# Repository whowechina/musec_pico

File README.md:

# Musec Pico - MUSECA Style Mini Controller
[点这里可以切换到中文版](README_CN.md)

There're two versions. Musec Pico uses 52mm spinners and Musec Pico+ uses 74mm spinners. They have the same structure and function the same.

Features:
* It's small but closely replicates the feel of the arcade controller.
* Built-in "spacebar" pedal.
* External pedal support through the 3.5mm jack.
* Full HID light support.
* Command line for configurations.
* All source files open.

Thanks to many respectful guys/companies who made their tools or materials free or open source (KiCad, OnShape, InkScape, Raspberry things).

Special thanks to community projects and developers.
And also these projects:
* RP_Silicon_KiCad: https://github.com/HeadBoffin/RP_Silicon_KiCad
* Type-C: https://github.com/ai03-2725/Type-C.pretty

## My Other Projects
You can check out my other cool projects.

* Popn Pico: https://github.com/whowechina/popn_pico
* IIDX Pico: https://github.com/whowechina/iidx_pico
* IIDX Teeny: https://github.com/whowechina/iidx_teeny
* Chu Pico: https://github.com/whowechina/chu_pico
* Mai Pico: https://github.com/whowechina/mai_pico
* Diva Pico: https://github.com/whowechina/diva_pico
* AIC Pico: https://github.com/whowechina/aic_pico
* Groove Pico: https://github.com/whowechina/groove_pico
* Geki Pico: https://github.com/whowechina/geki_pico
* Musec Pico: https://github.com/whowechina/musec_pico
* Ju Pico: https://github.com/whowechina/ju_pico
* Bishi Pico: https://github.com/whowechina/bishi_pico
* Nos Pico: https://github.com/whowechina/nos_pico

## **Disclaimer** ##
I made this project in my personal time with no financial benefit or sponsorship. I will continue to improve the project. I have done my best to ensure that everything is accurate and functional, there's always a chance that mistakes may occur. I cannot be held responsible for any loss of your time or money that may result from using this open source project. Thank you for your understanding.

## About the License
It's CC-NC. So DIY for yourself and for your friend, don't make money from it. And plagiarism that doesn’t even dare to mention the original author is not acceptable. Plase note that pooling orders and group buying for raw materials is acceptable. Selling off any leftover components without profit is also acceptable.

If you're interested in buying from me or some kind of commercial use, please contact me (Discord, QQ group, Wechat group or leave your contact in issue section).

## My Discord Invitation
https://discord.gg/M8f2PPQFEA

## HOW TO BUILD
### PCB and Components
* Go JLCPCB and make order with the gerber zip files (latest `Production\PCB\musec_pico_xxx.zip` for Musec Pico or `Production\PCB\musec_plus_xxx.zip` for Musec Pico+, and `Procution\PCB\musec_pedal_xxx.zip` for both versions), regular FR-4 board, black or white color, **1.6mm** thickness.  
  
* 1x Rasberry Pico Pi Pico or pin-to-pin compatible clones (U1).  
  https://www.raspberrypi.com/products/raspberry-pi-pico
* 1x USB Type-C socket (918-418K2023S40001 or KH-TYPE-C-16P)
* 28x WS2812B-3528 RGB LEDs (all RGB LEDs).
* 6x TMAG5273, all device versions (such as A1, B2, etc.) works, SOT23-6 (U3 to U7).  
* 12x 0603 0.1uF (0.1~1uF all fine) capacitors (all Capacitors).
* 2x 0603 5.1kohm resistors (R1, R2) for the USB.
* 2x 0603 5.1kohm resistors (R3, R4, 1k-20kohm all work fine) for I2C pull-up.
* 2x PJ-313 through-hole 3.5mm audio jacks (J2, J3).  
* 12x JST-SH1.0 4-pin right angle SMD connectors (JA1 to JA5, JB1 to JB5, Pedal, J1 on pedal board).  
  https://www.amazon.com/Kidisoii-Connector-Mounting-Vertical-SH1-0-SMT-Ver/dp/B0CQ28CCQG?th=1
* 6x JST-SH1.0 dual-end 4-pin cables, 60mm length * 5, and 100mm length * 1.
   The connector footprint on PCB also supports hand soldering. So if you can't find the connectors or the cables, you can solder the wires directly to the PCB.  
   RC hobby sites often have SH1.0 4P silicone cables, but with only one end connector. You can solder the other end to the PCB. It's still a good choice.
* 7x Kailh Choc v1. Choose heavy ones (70gf), I think the yellow with 70g force is the best.  
  
* For Musec Pico+, you can use one switch per button, or 2x switches per button to get more force.  
   
* 1x MX-compatible switch, I personally use Gateron POM CJ BOX.
* 1x Plate-mounting stabilizer for the MX switch, 6.25U.  
  https://www.amazon.com/GATERON-Stabilizer-Mechanical-Keyboard-Satellite/dp/B0C137DG5Q/

* This is how it looks after soldering (there might be changes in newer versions of PCB). I'm only showing the Musec Pico, but the Musec Pico+ is similar.  

* Becareful of 2 pin holes. It's a common oversight to either forget to solder them or to leave air bubbles during the process. To avoid this, solder slowly from one side of the hole, using minimal solder wire and a generous amount of flux.  

### Test the PCB
* You can test the PCB now, put the firmware in.
* All RGB LEDs should light up in a rainbow pattern.
* LEDs responds to the button presses.
* Musec Pico should be recognized as a USB HID device, here's the test page.  
  https://greggman.github.io/html5-gamepad-test/
* Move a magnetic screwdriver tip close to the TMAG5273 sensor, you'll notice the corresponding axis move in the test page. Please check all 5 sensors.

### Sensor PCB Separation
* If everthing works fine, you can cut off (or even bend and snap) the 5 small sensor boards from the main board.  

### 3D Printing
The following descriptions are for Musec Pico. If you're making Musec Pico+, please find the corresponding files with `+` in the name.

#### Printing parameters  
* PLA or PETG.
* Layer height: 0.2mm
* Support: Yes, always.
* Glue on bed: Yes, it prevents corner warping.
* Files are always in milimeter unit, not inch.

#### 5x Spinner Parts

* Keycap: `Production\3DPrint\musec_pico_keycap.stl`, white, 5 walls or >=90% infill. If you have multi-color system, print the 4 triangle marks on the top in gray. 
* Bearing Fixer: `Production\3DPrint\musec_pico_bearing_fixer.stl`, clear transparent.
* Shaft End: `Production\3DPrint\musec_pico_shaft_end_xxx.stl`, clear transparent, choose the one matches your magnet size.
* Lever: `Production\3DPrint\musec_pico_lever.stl`, clear transparent.
* Pad: `Production\3DPrint\musec_pico_pad.stl`, white, gray or black (so it won't affect the LED color).

#### Housing Parts
* Housing Bottom: `Production\3DPrint\musec_pico_bottom.stl`, black, use special support material for nicer screw hole surface.
* Housing Top: `Production\3DPrint\musec_pico_top.3mf`, gray, print up-side-down. If you have multi-color system, print the logo and lines in black.

#### Other Parts
Musec Pico and Musec Pico+ share these parts.
* Pedal: `Production\3DPrint\musec_pico_pedal.stl`, white, print upside down.
* Aux Buttons: `Production\3DPrint\musec_pico_aux.stl`, clear transparent, print upside down.

### Assembly
The following descriptions are for Musec Pico. But Musec Pico+ has the same internal structure, so the assembly is similar.

#### Other components needed
* **M2.5\*6mm screws** (5x for Musec Pico, 15x for Musec Pico+) for fixing the keycap to the bearing.
* 30x **M2\*8mm screws** for fixing the bearing and the sensor PCB to the lever.
* 15x **M3\*8mm screws** for fixing button pads to the bottom housing.
* 16x **M3\*(10-12mm) screws** for fixing the top and bottom housing and the pedal board to the bottom housing.  
* 5x 6700zz (10x15x4mm for Musec Pico), or 6702zz (15x21x4mm, for Musec Pico+) bearings for the spinner, just buy cheapest ones. They may come packed with a heavy weight oil that arrests rotation, this can be corrected by thoroughly degreasing the bearings and relubricating them with a lightweight oil like Super Lube ISO 68. For example, a soak and spin in 99% isopropyl alcohol, dry on a heated plate to remove the excess alcohol and thin and remaining grease, then a final wash in acetone (if you have all-metal bearings) and additional heated dry before relubricating will ensure the bearings spin freely.
  https://www.amazon.com/uxcell-6700ZZ-Groove-Bearings-Shielded/dp/B082PPYZQX/
* 5x round magnets, 5-7mm diameter for Musec Pico, 5mm only for Musec Pico+, 3mm or 4mm also works if you stick it well, 1.5mm or 2mm tall, MUST be radially/diametrically magnetized (N-S poles on the curved side).  
  https://wargameportal.com/products/special-diametrically-magnetized-50pcs-5mm-x-2mm-3-16-x-1-16-disc-magnets?variant=49014932209942
* 5x 2mm diameter steel shafts for the lever, 25mm length for Musec Pico, 40mm length for Musec Pico+.
* For Musec Pico+, you can use 5x 0.4mm\*5mm\*10mm\*6N (wire diameter\*outer diameter\*length\*number of coils) springs to increase the button force.  
* Some good tape (such as acetate tape or high-temp teflon tape) to fix the magnets in place.
* PTFE or UHMW tape for the sliding surfaces.
* Silicone anti-slip pads for the bottom.  
  
* Optional but good to have: plastic washer (ring pads), 0.5mm thick, 2.1~2.5mm inner diameter, 5-10mm outer diameter.  
  https://www.amazon.com/Bclla-Zkenshan-washers-Shock-Proof-Leak-Proof-Insulation/dp/B091Y7H9NX/
* Optional but good to have: A digital piano or music keyboard sustain pedal or a sewing machine pedal with 3.5mm jack. If it comes with 6.25mm jack, you also need a 6.25mm to 3.5mm adapter.

#### Steps
1. We'll start with the spinner part.  

2. Put the bearing into the bearing fixer, you'll need to bend the fixer a little bit to insert the bearing. Don't worry if the small connection part of the fixer breaks, it's fine. Then screw the bearing fixer to the lever.  

3. Screw the keycap using M2.5 screws mentioned earlier.  

4. Now insert the magnet into the slot at the center. It will be attracted to the screw head. But we still need some tape to fix it in place.  

5. Screw the sensor PCB to the lever and put a small piece of thin PTFE/UHMW tape on the surface. And lastly insert the shaft into the lever.  

6. Connect 5 SH1.0 cables to the main PCB. Install the main PCB and the pedal PCB to the bottom housing. Use another SH1.0 cable to connect the pedal PCB and the main PCB. The screwholes on pedal board is adjustable. Normally you need to install the pedal board a little higher.    

7. Connect the SH1.0 cables which are already connected to the main board to the sensor PCBs. And then push the lever shafts into the stands on the bottom housing. If you have keyboard lubricant, you can apply some to the shaft and the stand.  
     
   A pair of plastic washer will be helpful to prevent the lever from moving. They can also be used to adjust the lever position, compensating for the printing tolerance.  

8. Install the button pads using M3*8mm screws.  

9. Only for Musec Pico+, you can put springs onto the spring seats.

10. Install the top housing, you need to screw many M3 screws.  

11. Put the anti-slip pads on the bottom, right on top of the screws.  

#### Caution
* Each 3D printer and filament has its own tolerance. If you find the stem holes on the pedal keycap are too tight, use some needle or knife to enlarge them a little bit.
* Screws are easy to break the 3D printed parts. So don't screw them too tight. When you notice the resistance suddenly increases, stop screwing.

### Firmware
* UF2 file is in `Production\Firmware` folder.
* For the new build, hold the BOOTSEL button while connect the USB to a PC, there will be a disk named "RPI-RP2" showed up. Drag the UF2 firmware binary file into it. That's it. There's a small hole at the bottom side of the Musec Pico, it is facing right to the BOOTSEL button.
* If it's already running Musec Pico firmware, you can either use "update" in command line or hold down at least 4 buttons while connecting to USB to enter update mode.
* To access the command line, you can use this Web Serial Terminal to connect to the USB serial port of the Musec Pico. (Note: "?" is for help)  
  https://googlechromelabs.github.io/serial-terminal/

### Usage
* It's very simple. Just plug it in and play.
* You can set spin sensivity by "spin rate" command.
* Firmware identifies the polarity of the external pedal on power-up. Press Aux and Internal Pedal to re-identify the polarity.

## CAD Source File
I'm using OnShape free subscription. It's powerful but it can't archive original designs to local, so I can only share the link here. STL/DXF/DWG files are exported from this online document.  
  https://cad.onshape.com/documents/841383e62eb719d8b384c2c8/w/8c9b3131eb80c219de824619/e/8a5d9f0dffe483e0bce3630a

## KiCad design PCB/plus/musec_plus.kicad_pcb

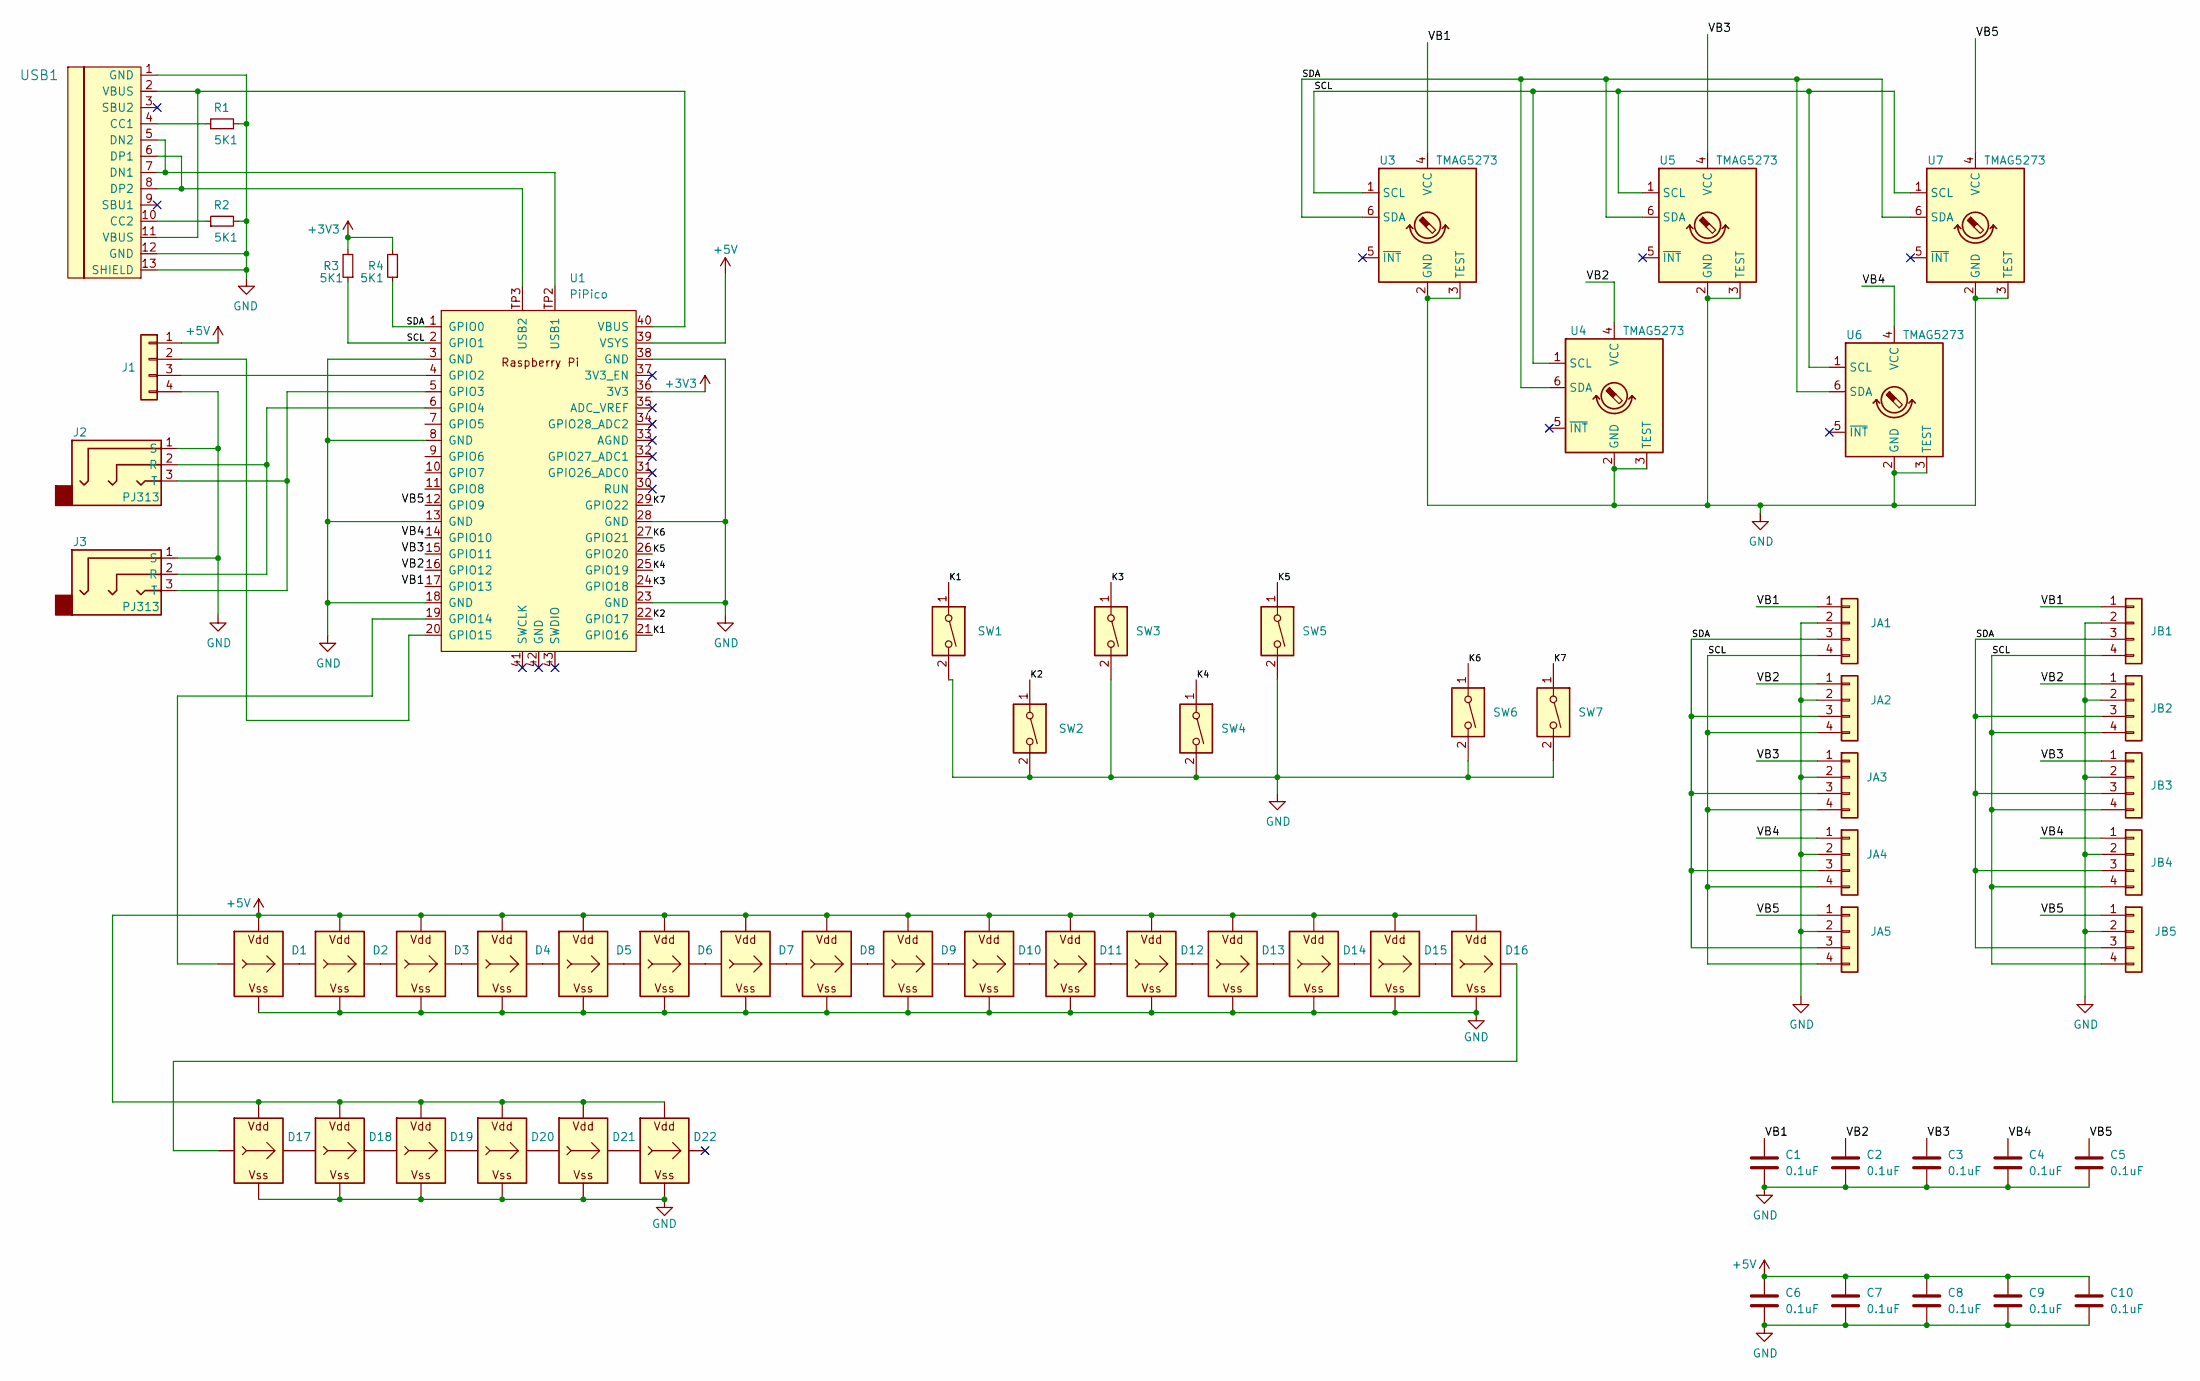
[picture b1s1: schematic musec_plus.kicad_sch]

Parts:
C1, C2, C3, C4, C5, C6, C7, C8, C9, C10: 0.1uF; C_0603_1608Metric_Pad1.08x0.95mm_HandSolder
D1, D2, D3, D4, D5, D6, D7, D8, D9, D10, D11, D12, D13, D14, D15, D16, D17, D18, D19, D20, D21, D22: WS2812B_Unified; WS2812B-2835
J1: Pedal; SH1.0_4P_Solder_Combo
J2, J3: PJ313
JA1, JA2, JA3, JA4, JA5: Conn_01x04; SH1.0_4P_Solder_Combo
JB1, JB2, JB3, JB4, JB5: Conn_01x04; SH1.0_4P_Solder_Combo
R1, R2, R3, R4: 5K1; R_0603_1608Metric_Pad0.98x0.95mm_HandSolder; LCSC C23186
SW1, SW2, SW3, SW4, SW5: SW_DIP_x01; Musec_ChocV1V2_x2_Combo
SW6, SW7: SW_DIP_x01; SW_Kailh_Choc_V1V2_1.00u_LED
U1: PiPico; RPi_Pico_SMD_Pins
U3, U4, U5, U6, U7: TMAG5273; TSOT-23-6_HandSoldering
USB1: U262-161N-4BVC11; HRO-TYPE-C-31-M-12-Assembly; LCSC C319148

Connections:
+3V3: R3.2, R4.2, U1.36 (3V3)
+5V: C6.1, C7.1, C8.1, C9.1, C10.1, D1.V (VDD), D2.V (VDD), D3.V (VDD), D4.V (VDD), D5.V (VDD), D6.V (VDD), D7.V (VDD), D8.V (VDD), D9.V (VDD), D10.V (VDD), D11.V (VDD), D12.V (VDD), D13.V (VDD), D14.V (VDD), D15.V (VDD), D16.V (VDD), D17.V (VDD), D18.V (VDD), D19.V (VDD), D20.V (VDD), D21.V (VDD), D22.V (VDD), J1.1, U1.39 (VSYS)
/K1: SW1.1, U1.21 (GPIO16)
/K2: SW2.1, U1.22 (GPIO17)
/K3: SW3.1, U1.24 (GPIO18)
/K4: SW4.1, U1.25 (GPIO19)
/K5: SW5.1, U1.26 (GPIO20)
/K6: SW6.1, U1.27 (GPIO21)
/K7: SW7.1, U1.29 (GPIO22)
/SCL: JA1.4, JA2.4, JA3.4, JA4.4, JA5.4, JB1.4, JB2.4, JB3.4, JB4.4, JB5.4, R3.1, U1.2 (GPIO1), U3.1 (SCL), U4.1 (SCL), U5.1 (SCL), U6.1 (SCL), U7.1 (SCL)
/SDA: JA1.3, JA2.3, JA3.3, JA4.3, JA5.3, JB1.3, JB2.3, JB3.3, JB4.3, JB5.3, R4.1, U1.1 (GPIO0), U3.6 (SDA), U4.6 (SDA), U5.6 (SDA), U6.6 (SDA), U7.6 (SDA)
/VB1: C1.1, JA1.1, JB1.1, U1.17 (GPIO13), U3.4 (VCC)
/VB2: C2.1, JA2.1, JB2.1, U1.16 (GPIO12), U4.4 (VCC)
/VB3: C3.1, JA3.1, JB3.1, U1.15 (GPIO11), U5.4 (VCC)
/VB4: C4.1, JA4.1, JB4.1, U1.14 (GPIO10), U6.4 (VCC)
/VB5: C5.1, JA5.1, JB5.1, U1.12 (GPIO9), U7.4 (VCC)
GND: C1.2, C2.2, C3.2, C4.2, C5.2, C6.2, C7.2, C8.2, C9.2, C10.2, D1.G (VSS), D2.G (VSS), D3.G (VSS), D4.G (VSS), D5.G (VSS), D6.G (VSS), D7.G (VSS), D8.G (VSS), D9.G (VSS), D10.G (VSS), D11.G (VSS), D12.G (VSS), D13.G (VSS), D14.G (VSS), D15.G (VSS), D16.G (VSS), D17.G (VSS), D18.G (VSS), D19.G (VSS), D20.G (VSS), D21.G (VSS), D22.G (VSS), J1.4, J2.1 (S), J3.1 (S), JA1.2, JA2.2, JA3.2, JA4.2, JA5.2, JB1.2, JB2.2, JB3.2, JB4.2, JB5.2, R1.2, R2.2, SW1.2, SW2.2, SW3.2, SW4.2, SW5.2, SW6.2, SW7.2, U1.3 (GND), U1.8 (GND), U1.13 (GND), U1.18 (GND), U1.23 (GND), U1.28 (GND), U1.38 (GND), U3.2 (GND), U3.3 (TEST), U4.2 (GND), U4.3 (TEST), U5.2 (GND), U5.3 (TEST), U6.2 (GND), U6.3 (TEST), U7.2 (GND), U7.3 (TEST), USB1.1 (GND), USB1.12 (GND), USB1.13 (SHIELD)
unnamed: D1.I (In), U1.19 (GPIO14)
unnamed: D1.O (Out), D2.I (In)
unnamed: D2.O (Out), D3.I (In)
unnamed: D3.O (Out), D4.I (In)
unnamed: D4.O (Out), D5.I (In)
unnamed: D5.O (Out), D6.I (In)
unnamed: D6.O (Out), D7.I (In)
unnamed: D7.O (Out), D8.I (In)
unnamed: D8.O (Out), D9.I (In)
unnamed: D9.O (Out), D10.I (In)
unnamed: D10.O (Out), D11.I (In)
unnamed: D11.O (Out), D12.I (In)
unnamed: D12.O (Out), D13.I (In)
unnamed: D13.O (Out), D14.I (In)
unnamed: D14.O (Out), D15.I (In)
unnamed: D15.O (Out), D16.I (In)
unnamed: D16.O (Out), D17.I (In)
unnamed: D17.O (Out), D18.I (In)
unnamed: D18.O (Out), D19.I (In)
unnamed: D19.O (Out), D20.I (In)
unnamed: D20.O (Out), D21.I (In)
unnamed: D21.O (Out), D22.I (In)
unnamed: J1.2, U1.20 (GPIO15)
unnamed: J1.3, U1.4 (GPIO2)
unnamed: J2.2 (R), J3.2 (R), U1.6 (GPIO4)
unnamed: J2.3 (T), J3.3 (T), U1.5 (GPIO3)
unnamed: U1.TP2 (USB1), USB1.5 (DN2), USB1.7 (DN1)
unnamed: U1.TP3 (USB2), USB1.6 (DP1), USB1.8 (DP2)
unnamed: U1.40 (VBUS), USB1.2 (VBUS), USB1.11 (VBUS)
unnamed: R1.1, USB1.4 (CC1)
unnamed: R2.1, USB1.10 (CC2)

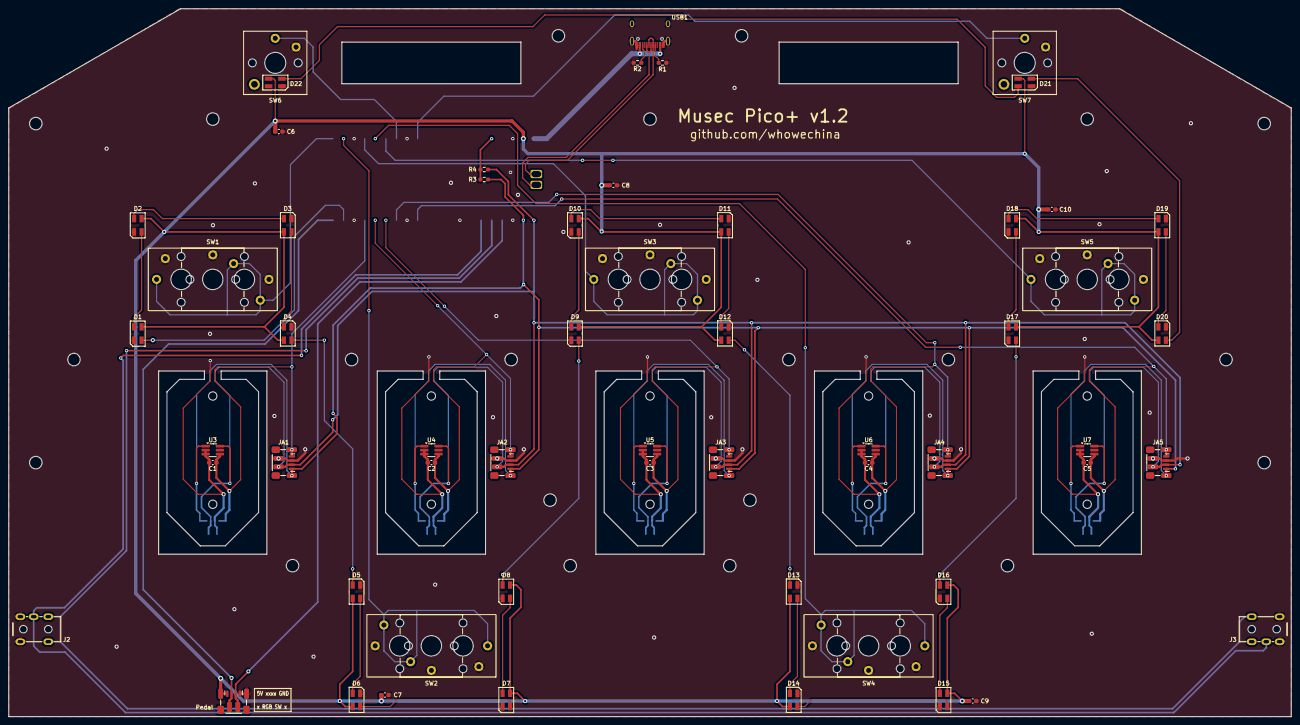
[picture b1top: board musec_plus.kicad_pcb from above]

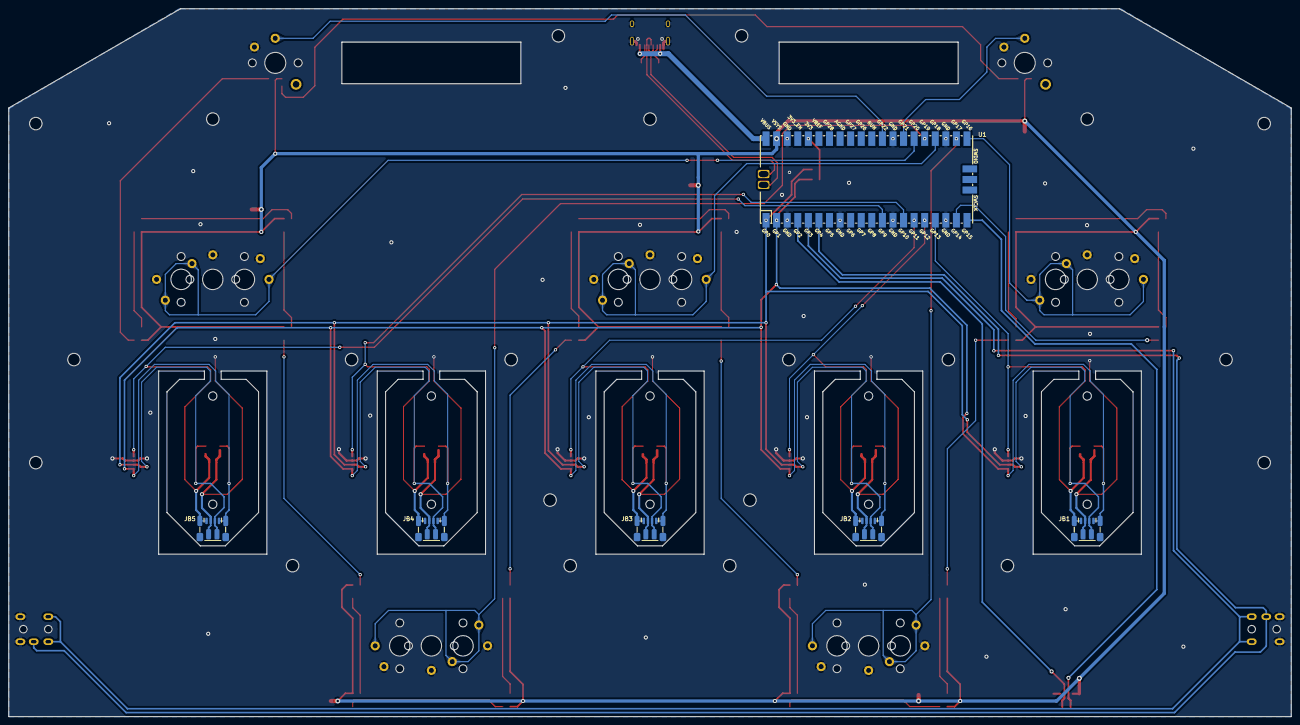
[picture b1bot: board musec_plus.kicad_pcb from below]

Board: 2 copper layers, 308.0 x 170.0 mm, 63 parts (6 on the bottom side), 48 nets.

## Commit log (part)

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2024-09-26 PCB work starts
2024-09-27 Firmware, tmag5273 works
2024-09-27 PCB progress 70%
2024-09-28 PCB almost done (95%)
2024-09-28 PCB v1.0
2024-09-29 Tmag5273 can change address
2024-10-03 Automatic tmag5273 multiple address handling
2024-10-05 Minor style issue fix
2024-10-05 Multiple spin works
2024-10-05 Pedal button
2024-10-06 Firmware working
2024-10-07 PCB v1.1 to support pedal
2024-10-09 PCB v1.2 (internal pedal connector and light)
2024-10-09 Pedal, spin and light
2024-10-09 Remove usb report debug print
2024-10-09 Int and Ext pedals combined in logic
2024-10-09 Auto external pedal polarity
2024-10-10 PCB V1.21, larger thru-holes for PJ313
2024-10-10 Move main PCB to a sub-folder
2024-10-10 Pedal board v1.0
2024-10-13 Pedal polarity reset at runtime1
2024-10-13 Spin reverse setting works
2024-10-14 PCB v1.22 for better PJ313 footprint
2024-10-15 PCB v1.23 better footprints
2024-10-15 English guide done.
2024-10-15 Fighting github markdown, again
2024-10-15 Shorter controller name
2024-10-16 3D Print files
2024-10-16 Add more magnet option
2024-10-16 Shaft lub and limiter
2024-10-16 Chinese version guide done
2024-10-16 Pedal polarity description
2024-10-16 External pedal option
2024-10-17 Caution and markdown cleanup
2024-10-17 Better screw holes
2024-10-17 Pedal PCB v1.1 (fix stabilizer position)
2024-10-17 Pedal PCB v1.2 (more accurate holes)
2024-10-18 Stronger lever support
2024-10-18 Discord invitation
2024-10-18 Small formatting update
2024-10-18 Remove unnecessary wording
2024-10-22 Plastic washer in guide
2024-10-23 PCB v1.3 (a little bit easier soldering)
2024-11-11 Change link to JST sockets
    The current link is for vertical sockets when it appears as though right angle ones are intended.
2024-11-12 More accurate SH1.0 connector description
2024-11-16 Provide instructions for bearing prep.
    The uxcell bearings from Amazon in the US come lubed with a heavy oil that prevents free spinning, so I thought I'd give some suggestions on how to improve the bearings you get instead of resorting t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
2024-11-16 Add note about acetone
    Acetone should only be used on all metal bearings since it's a polar solvent.
2024-11-19 Bearing oil replacement guide in CN
2024-11-23 Cross-reference
2024-12-01 Fix getchar return handling
2025-01-04 Better polling rate
2025-02-06 Stronger lever
2025-02-09 Better shaft slits (avoid break)
2025-03-16 Edge-triggered HID report
2025-03-16 Slower I2C clock for some slow sensors
2025-04-04 Cross-reference to new projects
2025-05-04 Move original PCB to pico folder
2025-05-04 Start PCB work for Musec Pico Plus
2025-05-05 Musec Pico+ PCB v1.0
2025-05-17 Guide for Musec Pico+
2025-05-17 Musec Pico+ PCB v1.01
2025-05-17 Fix bearing models for Musec Pico+
2025-05-17 Correct steel shaft length for Musec Pico+
2025-05-17 Add description for shared parts
2025-05-17 Small delay for better boot up
2025-06-07 Fix shaft end screw sink for Musec+
2025-06-12 Bigger pads for Musec Pico+
2025-10-16 Pedal v1.21, better SH1.0 footprint
2025-11-25 Explicit I2C Pull-ups
2025-11-27 I2C speed options
2026-01-22 pedal pcb v1.22, finetune
2026-05-29 Fix the R3/R4 value mistake
2026-05-29 Allow all tmag5273 versions
2026-05-29 Make tmag5273A1 version as first search
